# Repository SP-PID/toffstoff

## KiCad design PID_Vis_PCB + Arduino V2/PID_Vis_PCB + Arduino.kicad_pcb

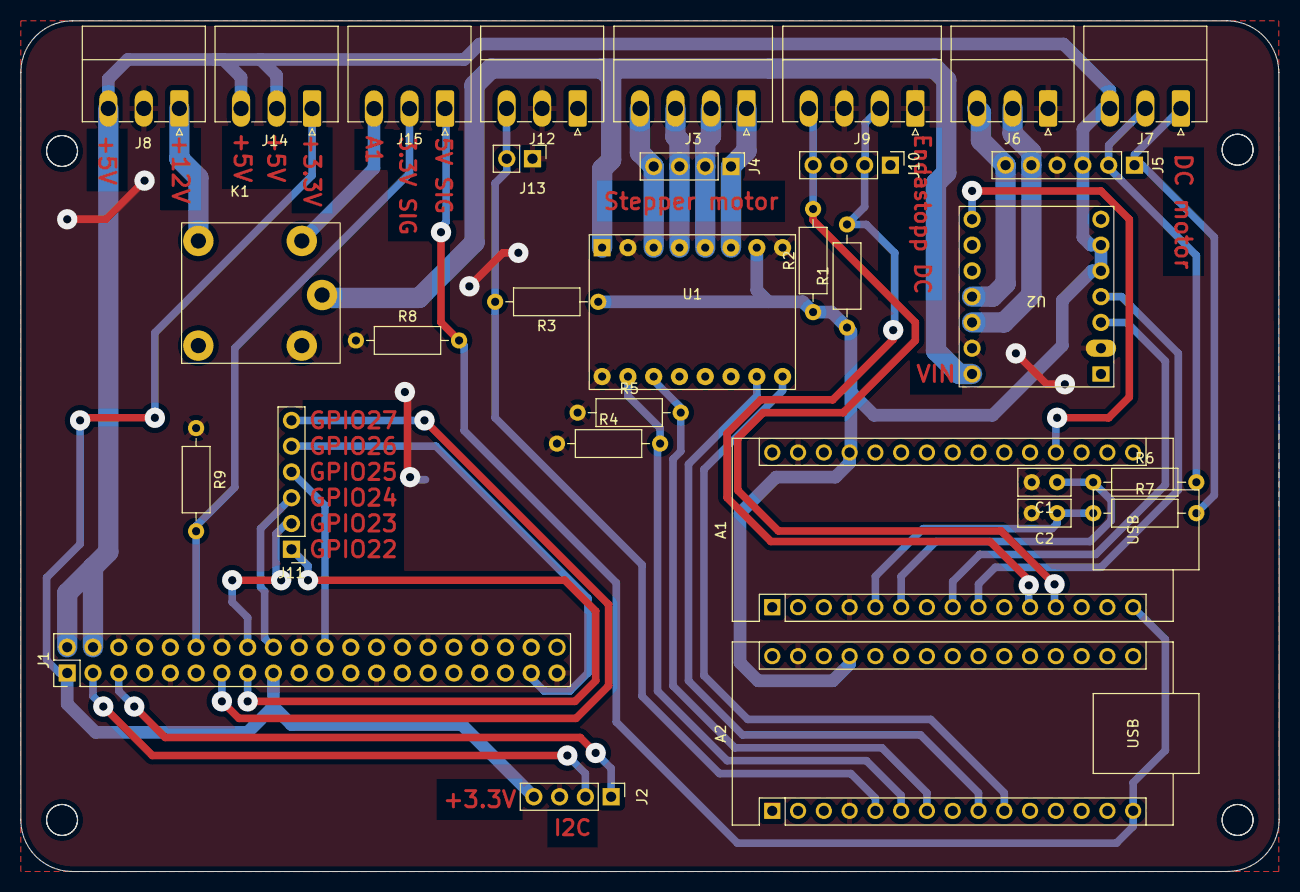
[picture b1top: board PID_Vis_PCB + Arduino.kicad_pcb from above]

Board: 2 copper layers, 124.0 x 83.8 mm, 31 parts (0 on the bottom side), 36 nets.

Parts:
A1, A2: Arduino_Nano_v2.x; Arduino_Nano
C1, C2: 50pF; C_Disc_D5.0mm_W2.5mm_P2.50mm
J1: Raspberry_Pi_2_3; PinHeader_2x20_P2.54mm_Vertical
J2, J4, J10: Conn_01x04_Male; PinHeader_1x04_P2.54mm_Vertical
J3, J9: Conn_01x04_Male; PhoenixContact_MC_1,5_4-G-3.5_1x04_P3.50mm_Horizontal
J5, J11: Conn_01x06_Male; PinHeader_1x06_P2.54mm_Vertical
J6, J7, J8, J12, J14, J15: Conn_01x03_Male; PhoenixContact_MC_1,5_3-G-3.5_1x03_P3.50mm_Horizontal
J13: Conn_01x02_Male; PinHeader_1x02_P2.54mm_Vertical
K1: FINDER-36.11; Relay_SRA-05VDC-CL
R1, R2, R3, R4, R5, R8, R9: 10k; R_Axial_DIN0207_L6.3mm_D2.5mm_P10.16mm_Horizontal
R6, R7: 2R2; R_Axial_DIN0207_L6.3mm_D2.5mm_P10.16mm_Horizontal
U1: TMC2208_-_Driver_board; TMC2208 - Driverboard
U2: DRV8874_Single_Brushed_DC_Motor_Driver; DRV8874 Single Brushed DC Motor Driver

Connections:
+3.3V: J1.1 (3V3), J1.17 (3V3), J2.4, J14.1
+5V: A1.27 (+5V), A2.27 (+5V), J1.2 (5V), J1.4 (5V), J5.3, J7.3, J8.3, J14.2, J14.3, R1.1, R2.1, R3.1, U1.7 (VIO), U2.5 (PMODE), U2.6 (SLEEP)
+12V: K1.11, U1.1 (VM), U2.14 (VIN)
GND: A1.4 (GND), A1.29 (GND), A2.4 (GND), A2.29 (GND), C1.2, C2.2, J1.6 (GND), J1.9 (GND), J1.14 (GND), J1.20 (GND), J1.25 (GND), J1.30 (GND), J1.34 (GND), J1.39 (GND), J2.3, J5.4, J6.1, J8.2, J9.1, J9.3, J10.1, J10.3, J12.2, J13.1, K1.A2, R4.1, R5.1, R8.1, R9.1, U1.2 (GND), U1.8 (GND), U1.16 (EN), U2.2 (GND), U2.13 (GND)
unnamed: A1.5 (D2), C2.1, R7.1
unnamed: A1.6 (D3), C1.1, R6.1
unnamed: A1.8 (D5), U2.3 (EN/IN1)
unnamed: A1.9 (D6), U2.4 (PH/IN2)
unnamed: A1.11 (D8), J9.2, J10.2, R1.2
unnamed: A1.12 (D9), J9.4, J10.4, R2.2
unnamed: A1.15 (D12), A2.15 (D12), J15.1, R8.2
unnamed: A1.19 (A0), U2.8 (CS)
unnamed: A2.5 (D2), J12.3, J13.2, R3.2
unnamed: A2.9 (D6), U1.10 (STEP)
unnamed: A2.10 (D7), U1.9 (DIR)
unnamed: J1.3 (SDA/GPIO2), J2.2
unnamed: J1.5 (SCL/GPIO3), J2.1
unnamed: J1.12 (GPIO18/PWM0), J15.2, R9.2
unnamed: J1.13 (GPIO27), J11.6
unnamed: J1.15 (GPIO22), J11.1
unnamed: J1.16 (GPIO23), J11.2
unnamed: J1.18 (GPIO24), J11.3
unnamed: J1.22 (GPIO25), J11.4
unnamed: J1.37 (GPIO26), J11.5
unnamed: J5.1, J7.1, R7.2
unnamed: J5.2, J7.2, R6.2
unnamed: J5.5, J6.2, U2.12 (OUT1)
unnamed: J5.6, J6.3, U2.11 (OUT2)
unnamed: J8.1, K1.14
unnamed: J15.3, K1.A1
unnamed: A2.6 (D3), R4.2, U1.15 (MS1)
unnamed: A2.7 (D4), R5.2, U1.14 (MS2)
unnamed: J3.4, J4.4, U1.3 (M1B)
unnamed: J3.3, J4.3, U1.4 (M1A)
unnamed: J3.2, J4.2, U1.5 (M2A)
unnamed: J3.1, J4.1, U1.6 (M2B)

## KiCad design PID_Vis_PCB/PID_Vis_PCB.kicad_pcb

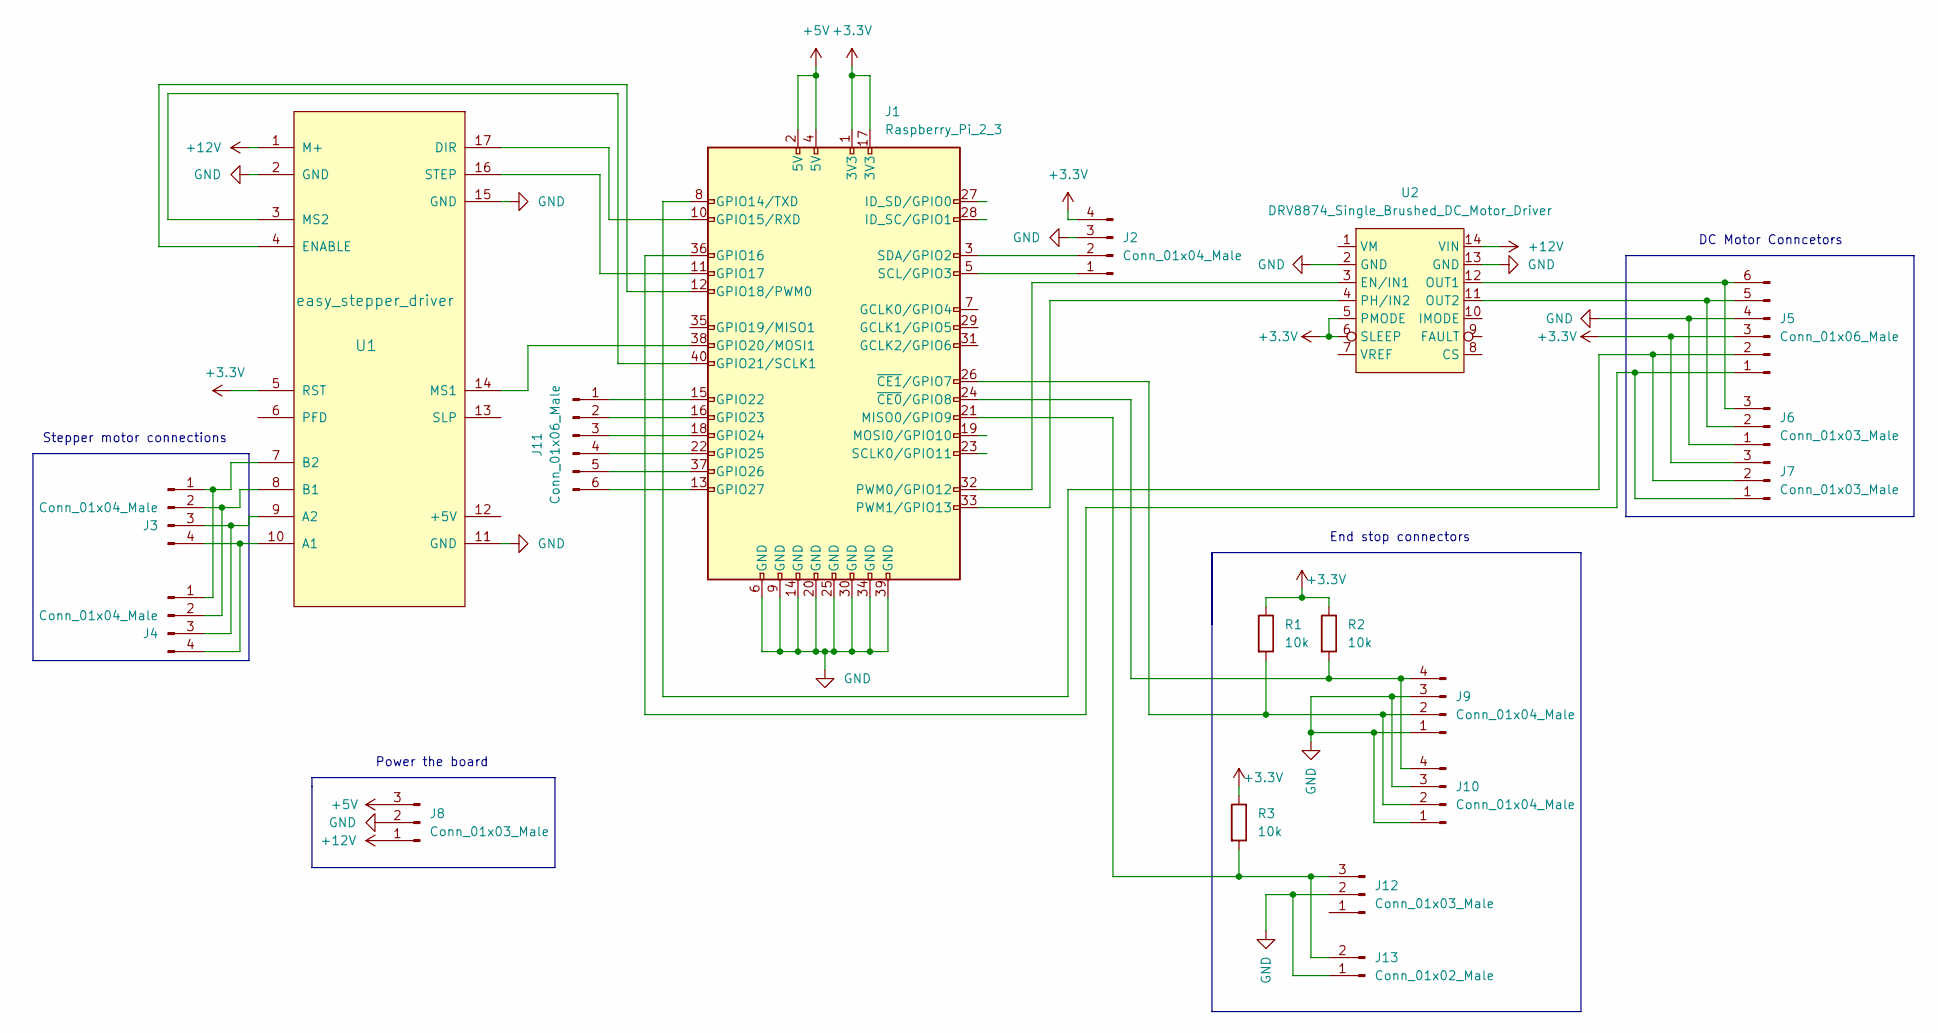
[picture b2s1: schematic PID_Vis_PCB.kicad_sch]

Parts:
J1: Raspberry_Pi_2_3; PinHeader_2x20_P2.54mm_Vertical
J2, J4, J10: Conn_01x04_Male; PinHeader_1x04_P2.54mm_Vertical
J3, J9: Conn_01x04_Male; PhoenixContact_MC_1,5_4-G-3.5_1x04_P3.50mm_Horizontal
J5, J11: Conn_01x06_Male; PinHeader_1x06_P2.54mm_Vertical
J6, J7, J8, J12: Conn_01x03_Male; PhoenixContact_MC_1,5_3-G-3.5_1x03_P3.50mm_Horizontal
J13: Conn_01x02_Male; PinHeader_1x02_P2.54mm_Vertical
R1, R2, R3: 10k; R_Axial_DIN0207_L6.3mm_D2.5mm_P10.16mm_Horizontal
U1: easy_stepper_driver
U2: DRV8874_Single_Brushed_DC_Motor_Driver; DRV8874 Single Brushed DC Motor Driver

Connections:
+3.3V: J1.1 (3V3), J1.17 (3V3), J2.4, J5.3, J7.3, R1.1, R2.1, R3.1, U1.5 (RST), U2.5 (PMODE), U2.6 (SLEEP)
+5V: J1.2 (5V), J1.4 (5V), J8.3
+12V: J8.1, U1.1 (M+), U2.14 (VIN)
GND: J1.6 (GND), J1.9 (GND), J1.14 (GND), J1.20 (GND), J1.25 (GND), J1.30 (GND), J1.34 (GND), J1.39 (GND), J2.3, J5.4, J6.1, J8.2, J9.1, J9.3, J10.1, J10.3, J12.2, J13.1, U1.2 (GND), U1.11 (GND), U1.15 (GND), U2.2 (GND), U2.13 (GND)
unnamed: J1.3 (SDA/GPIO2), J2.2
unnamed: J1.5 (SCL/GPIO3), J2.1
unnamed: J1.10 (GPIO15/RXD), U1.17 (DIR)
unnamed: J1.11 (GPIO17), U1.16 (STEP)
unnamed: J1.12 (GPIO18/PWM0), U1.4 (ENABLE)
unnamed: J1.13 (GPIO27), J11.6
unnamed: J1.15 (GPIO22), J11.1
unnamed: J1.16 (GPIO23), J11.2
unnamed: J1.18 (GPIO24), J11.3
unnamed: J1.21 (MISO0/GPIO9), J12.3, J13.2, R3.2
unnamed: J1.22 (GPIO25), J11.4
unnamed: J1.24 (~CE0/GPIO8), J9.4, J10.4, R2.2
unnamed: J1.33 (PWM1/GPIO13), U2.4 (PH/IN2)
unnamed: J1.36 (GPIO16), J5.1, J7.1
unnamed: J1.37 (GPIO26), J11.5
unnamed: J1.38 (GPIO20/MOSI1), U1.14 (MS1)
unnamed: J1.40 (GPIO21/SCLK1), U1.3 (MS2)
unnamed: J3.1, J4.1, U1.7 (B2)
unnamed: J3.2, J4.2, U1.8 (B1)
unnamed: J3.3, J4.3, U1.9 (A2)
unnamed: J3.4, J4.4, U1.10 (A1)
unnamed: J1.8 (GPIO14/TXD), J5.2, J7.2
unnamed: J5.5, J6.2, U2.11 (OUT2)
unnamed: J5.6, J6.3, U2.12 (OUT1)
unnamed: J1.26 (~CE1/GPIO7), J9.2, J10.2, R1.2
unnamed: J1.32 (PWM0/GPIO12), U2.3 (EN/IN1)

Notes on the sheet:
Power the board
DC Motor Conncetors
End stop connectors
Stepper motor connections

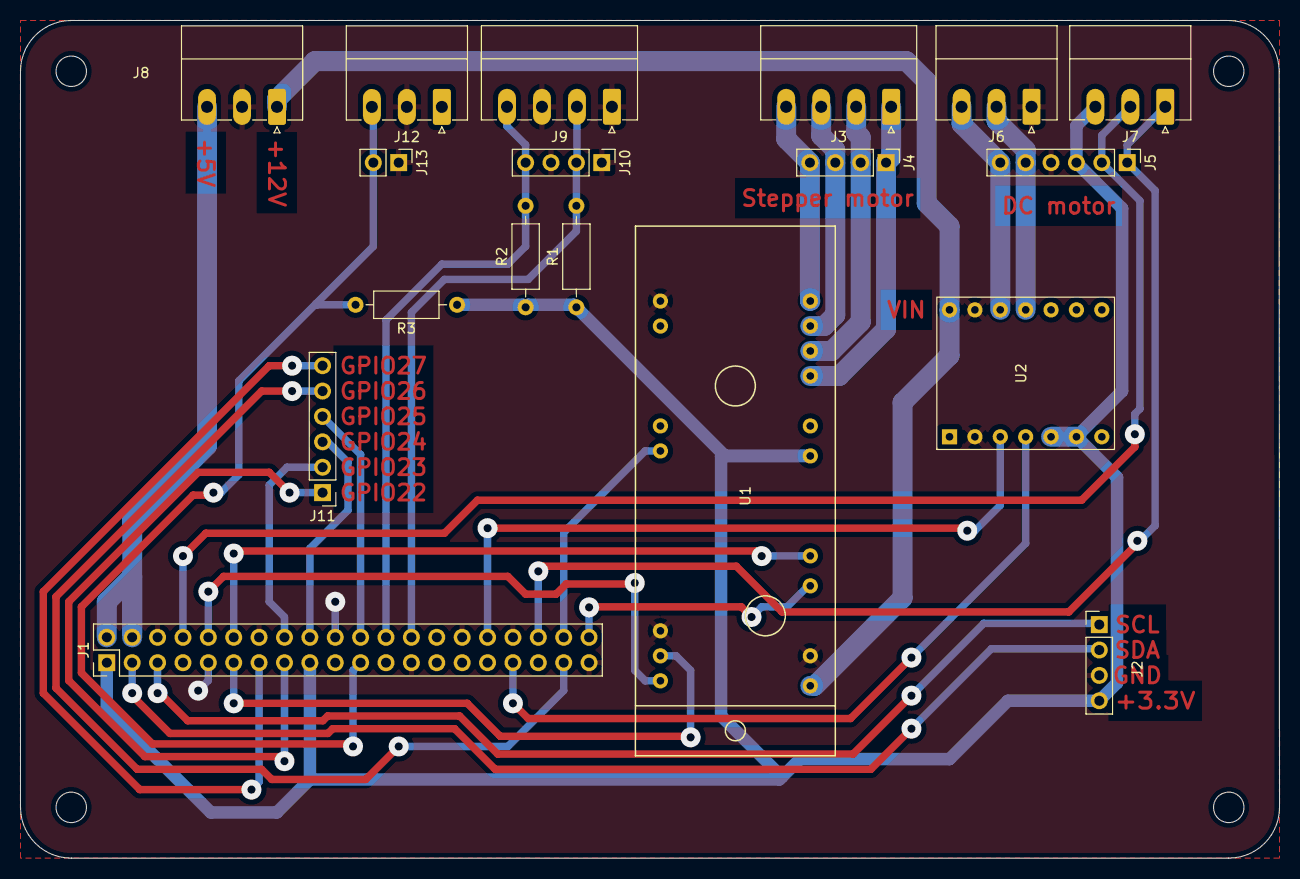
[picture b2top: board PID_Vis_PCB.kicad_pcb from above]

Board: 2 copper layers, 126.0 x 83.8 mm, 18 parts (0 on the bottom side), 30 nets.

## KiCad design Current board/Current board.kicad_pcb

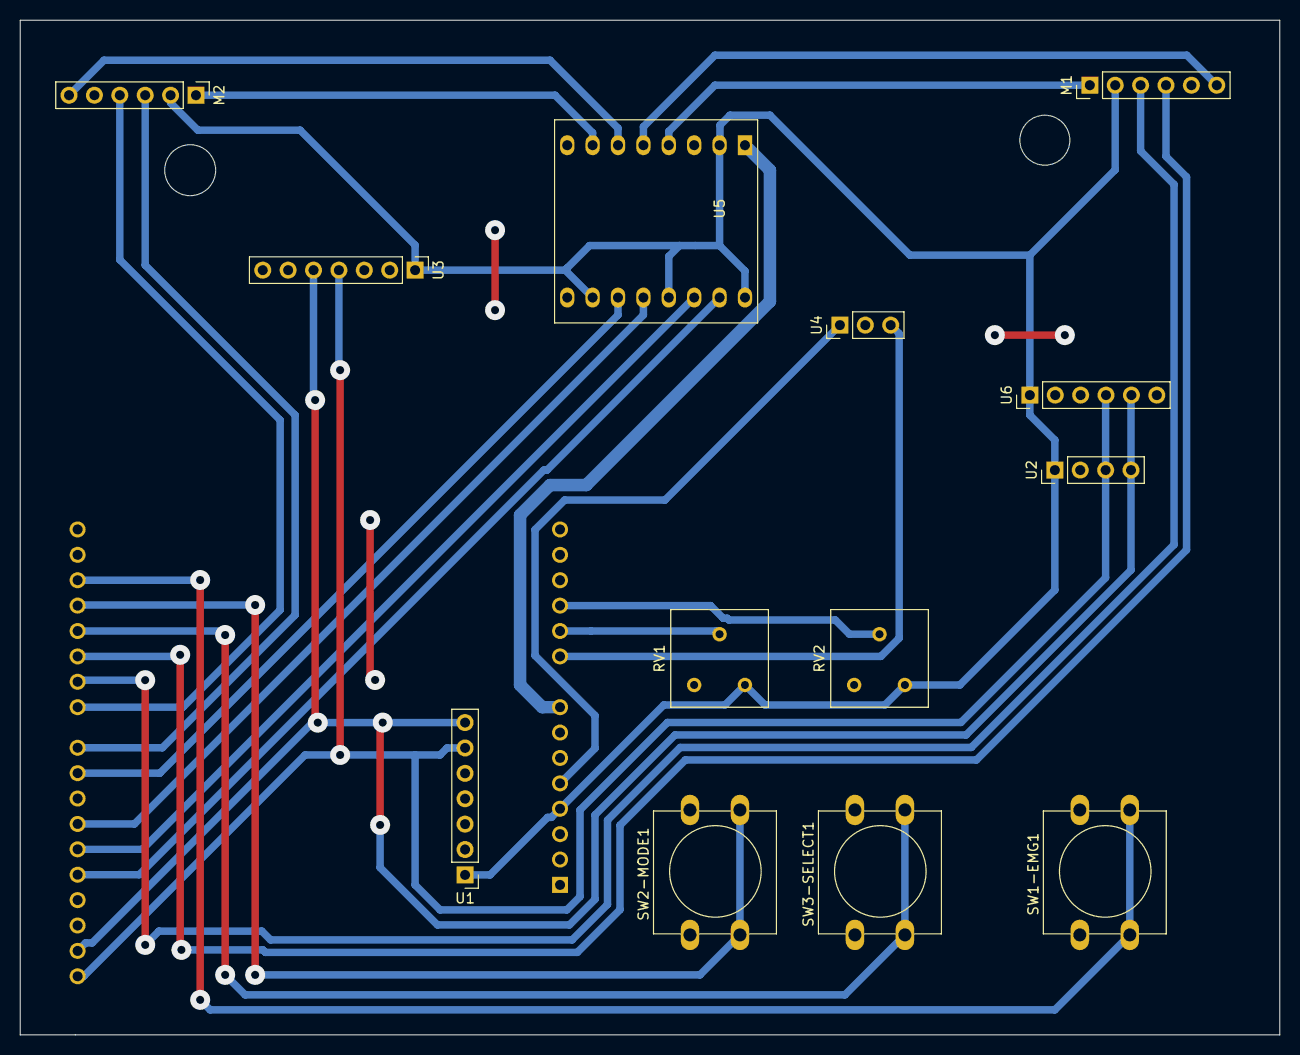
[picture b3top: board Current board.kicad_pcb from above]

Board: 2 copper layers, 126.0 x 101.5 mm, 14 parts (1 on the bottom side), 23 nets.

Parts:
A1: Metro_M4_Airlift; Arduino_UNO_R3
M1, M2: Micromotr_encoder; PinHeader_1x06_P2.54mm_Vertical
RV1, RV2: R_POT; Potentiometer_Bourns_3386F_Vertical
SW1-EMG1, SW2-MODE1, SW3-SELECT1: SW_MEC_5E; SW_PUSH-12mm
U1: MPL3115A2_modoule; PinHeader_1x07_P2.54mm_Vertical
U2: SSD1306_Display; PinHeader_1x04_P2.54mm_Vertical
U3: TCS34725_RGBsensor; PinHeader_1x07_P2.54mm_Vertical
U4: 2Y0A02_F22-IR distance_sensor; PinHeader_1x03_P2.54mm_Vertical
U5: TB6612FNG_Board; SparkfunTB6612FNG
U6: FXOS8700-DOF; PinHeader_1x06_P2.54mm_Vertical

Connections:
+3V3: A1.4 (3V3), M1.2 (+3v3_encoder), M2.2 (+3v3_encoder), RV1.1, RV2.1, U1.1 (Vin), U2.1 (VCC), U3.1 (Vin), U5.2 (VCC), U5.10 (PWMB), U5.13 (STBY), U5.16 (PWMA), U6.1 (Vin)
+5V: A1.5 (+5V), U4.1 (Vcc)
+BATT: A1.8 (VIN), U5.1 (VM1)
GND: A1.6 (GND), A1.7 (GND), A1.29 (GND), M1.5 (GND_encoder), M2.5 (GND_encoder), RV1.3, RV2.3, SW1-EMG1.1, SW1-EMG1.2, SW2-MODE1.1, SW2-MODE1.2, SW3-SELECT1.1, SW3-SELECT1.2, U1.2 (GND), U2.2 (GND), U3.2 (GND), U4.2 (GND), U5.3 (GND), U5.8 (GND), U5.9 (GND), U6.3 (GND)
unnamed: A1.9 (A0), U4.3 (SIG_out)
unnamed: A1.10 (A1), RV1.2
unnamed: A1.11 (A2), RV2.2
unnamed: A1.17 (D2), SW1-EMG1.3 (K), SW1-EMG1.4 (A)
unnamed: A1.18 (D3), SW2-MODE1.3 (K), SW2-MODE1.4 (A)
unnamed: A1.19 (D4), SW3-SELECT1.3 (K), SW3-SELECT1.4 (A)
unnamed: A1.20 (D5), M1.4 (Phase_B)
unnamed: A1.21 (D6), M1.3 (Phase_A)
unnamed: A1.26 (D11), U5.12 (BIN1)
unnamed: A1.27 (D12), U5.14 (AIN1)
unnamed: A1.28 (D13), U5.15 (AIN2)
unnamed: A1.31 (SDA), U1.7 (SDA), U2.4 (SDA), U3.5 (SDA), U6.5 (SDA)
unnamed: A1.32 (SCL), U1.6 (SCL), U2.3 (SCL), U3.4 (SCL), U6.4 (SCL)
unnamed: M1.1 (M1), U5.4 (AO1)
unnamed: M1.6 (M2), U5.5 (AO2), U5.6 (AO2)
unnamed: M2.1 (M1), U5.7 (BO1)
unnamed: A1.23 (D8), M2.3 (Phase_A)
unnamed: A1.22 (D7), M2.4 (Phase_B)
unnamed: A1.24 (D9), U5.11 (BIN2)

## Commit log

2022-11-22 PID reglir
2022-11-22 afi þinn er amma mín
2022-11-22 helvítis weird
2022-11-22 Árni að hjálpa
2022-11-22 suck it
2022-11-22 Endastopp
2022-11-22 Added endstops for óli
2022-11-22 FLag og calibrate ?
2022-11-24 Newest
2022-11-24 ekki á toppnum
2022-11-24 dfghj
2022-11-24 testaðu þetta tussan þín
2022-11-25 Loading screen added
2022-11-25 Loading screen ready!
2022-11-28 Baetti vid tokkum
2022-11-28 bjó til main.py
2022-11-28 Einhverjar breitingar
2022-11-28 Breita shit
2022-11-28 laga SP takkan
2022-11-28 Var að breyta. ætla að gera branch
2022-11-29 added .csv writer
2022-11-30 .csv writer working
2022-11-30 Coding lika a G
2022-11-30 Upgrades! upgrades
2022-12-01 running
2022-12-01 updated GUI
2022-12-06 improvements
2022-12-06 stuff
2022-12-07 vinna i final code
2022-12-07 testyboy update
2022-12-07 cdcd
2022-12-07 ffffffd
2022-12-07 auto assign arduino
2022-12-08 fixing
2022-12-08 hlutir farnri ar[ virkar
2022-12-08 auto second identify
2022-12-08 better gui
2022-12-08 Finally auto detect virkar
2022-12-09 asd# Please enter the commit message for your changes. Lines starting
2022-12-09 Schematic change
